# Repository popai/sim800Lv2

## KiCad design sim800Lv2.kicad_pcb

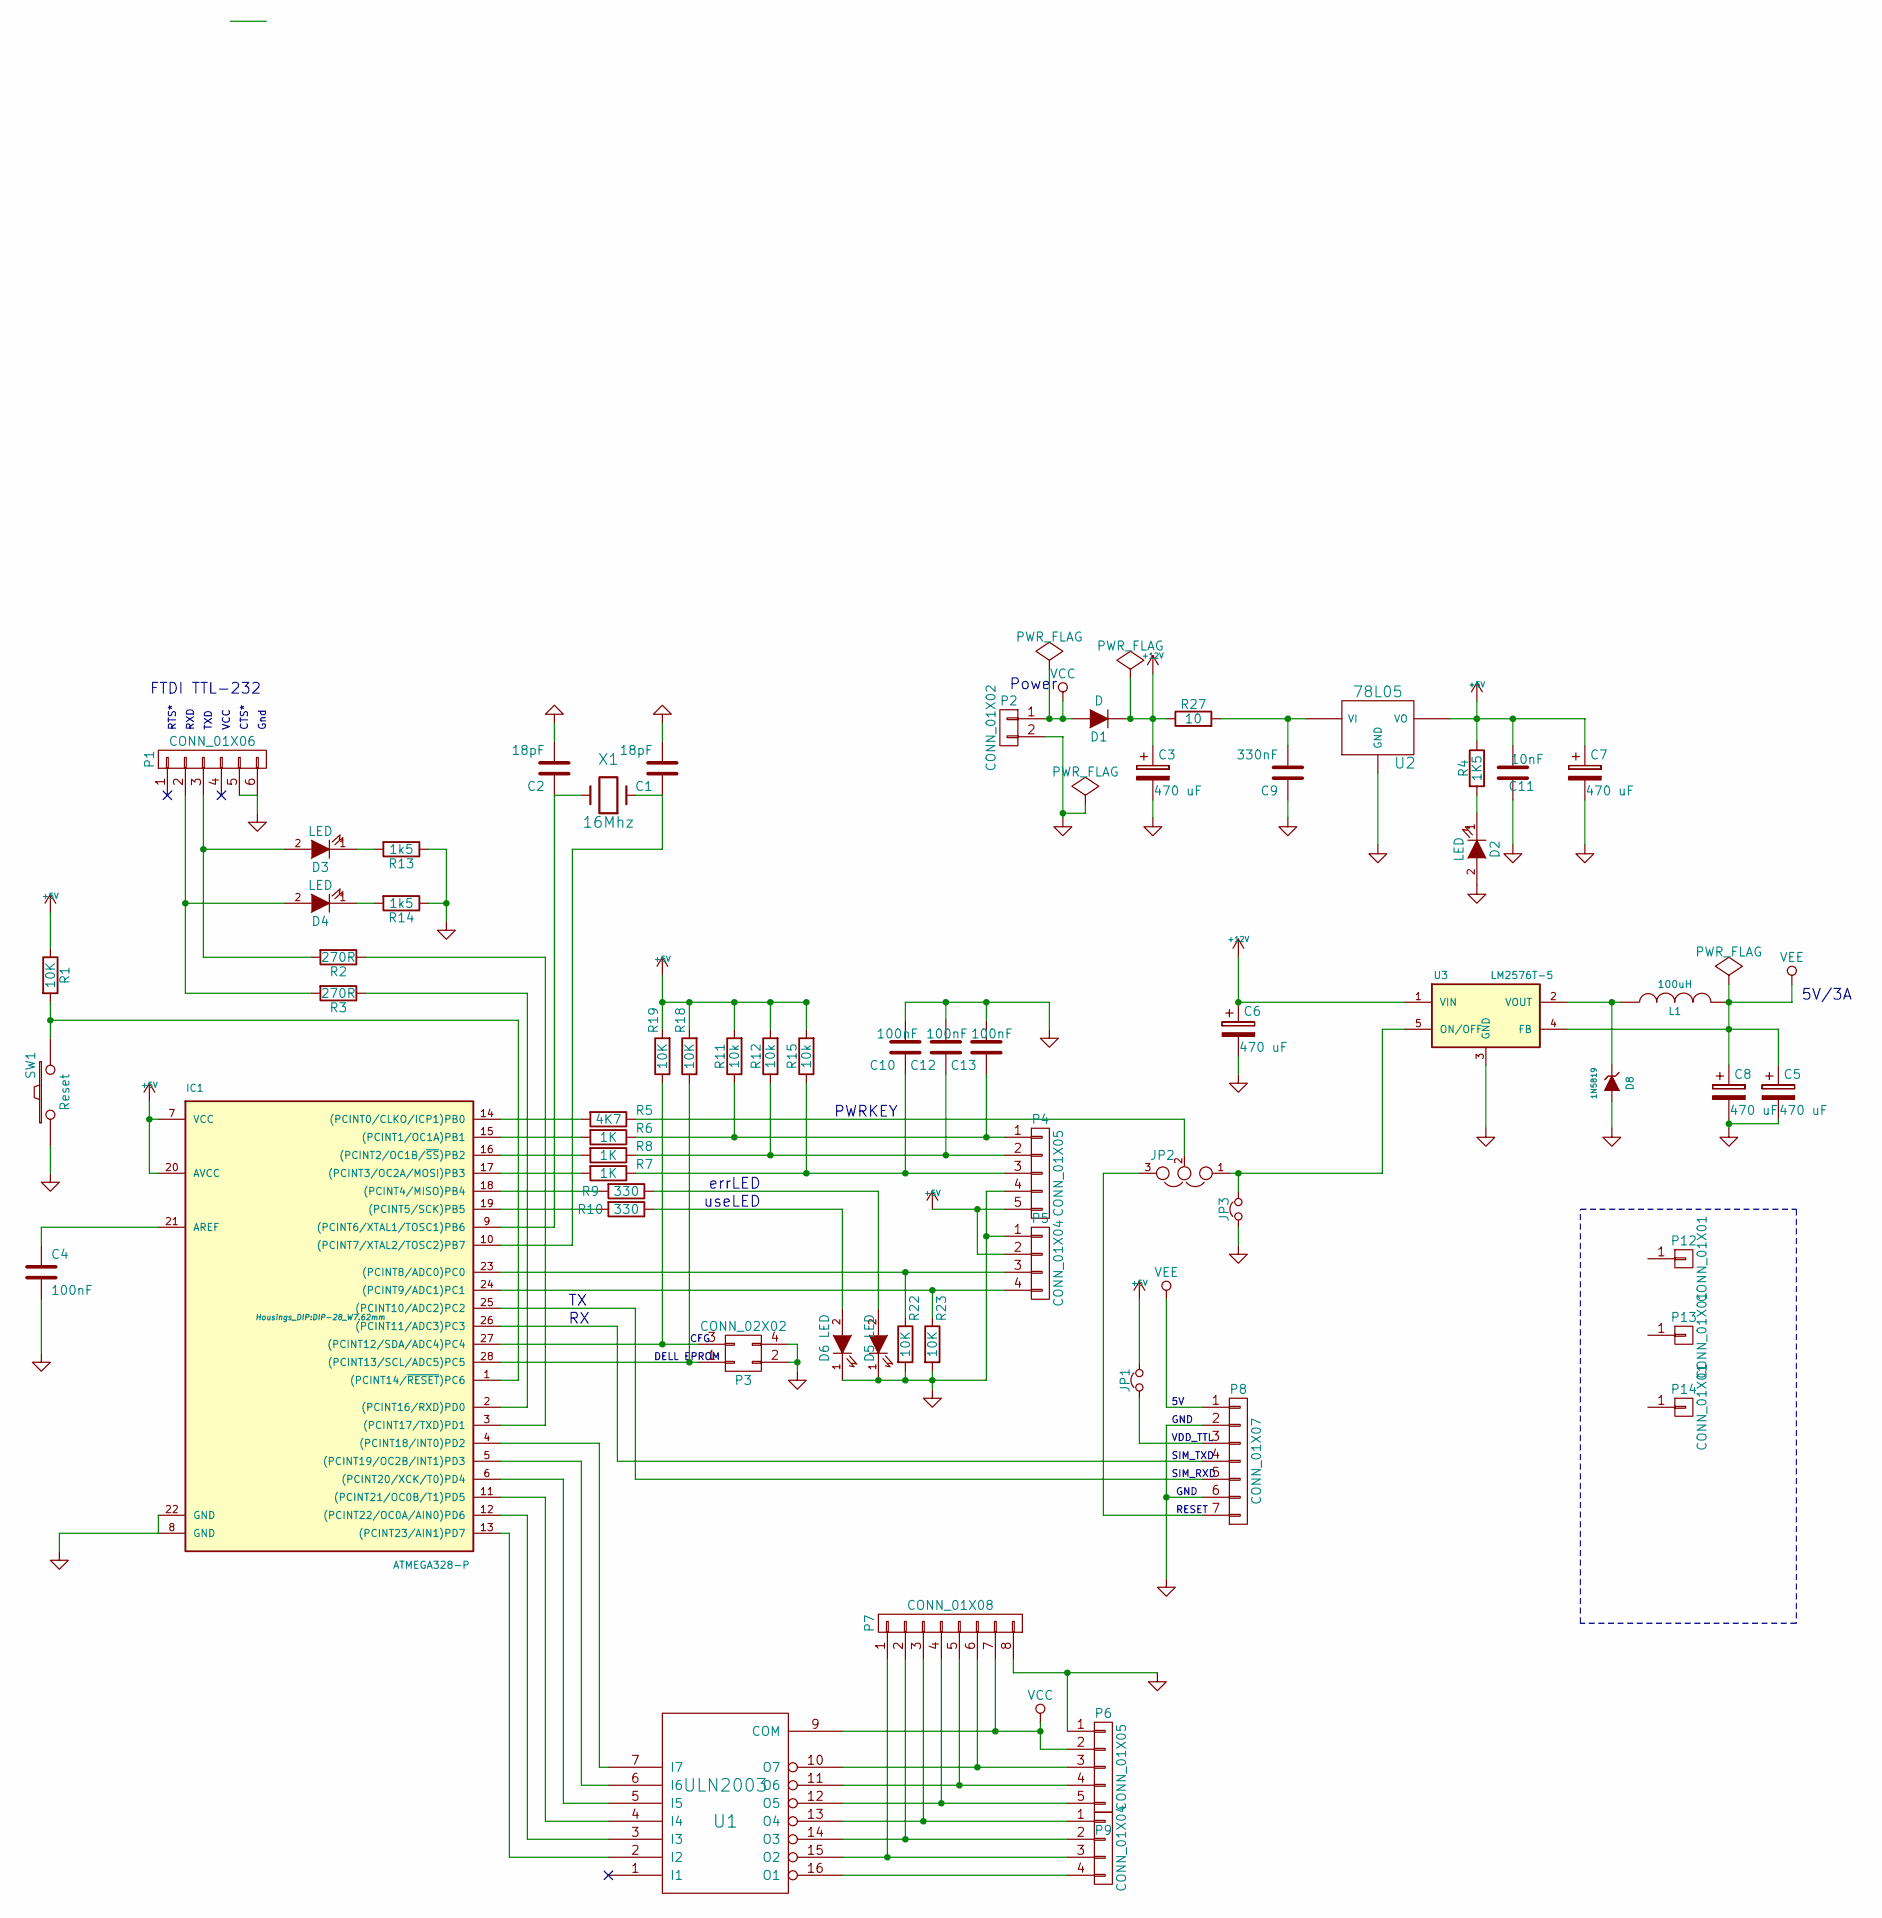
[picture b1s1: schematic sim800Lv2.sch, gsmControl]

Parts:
C1, C2: 18pF; C_Disc_D3_P2.5
C3, C5, C6, C7, C8: 470 uF; C_Radial_D8_L11.5_P3.5
C4, C10, C12, C13: 100nF; C_Rect_L7_W2_P5
C9: 330nF; C_Rect_L7_W2_P5
C11: 10nF; C_Rect_L7_W2_P5
D1: D; Diode_DO-35_SOD27_Horizontal_RM10
D2, D3, D4, D5, D6: LED; LED-3MM
D8: 1N5819; Diode_DO-35_SOD27_Horizontal_RM10
IC1: ATMEGA328-P; DIP-28_W7.62mm
JP1: Jumper_NC_Small; Resistor_Horizontal_RM7mm
JP2: JUMPER3; Pin_Header_Straight_1x03
JP3: Jumper_NC_Small; R_0603_HandSoldering
L1: 100uH; INDUCTOR_V
P1: CONN_01X06; Pin_Header_Straight_1x06
P2: CONN_01X02; Socket_MOLEX-KK-RM3-96mm_Lock_2pin_straight
P3: CONN_02X02; Pin_Header_Straight_2x02
P4, P6: CONN_01X05; Socket_MOLEX-KK-RM3-96mm_Lock_5pin_straight
P5, P9: CONN_01X04; Socket_MOLEX-KK-RM3-96mm_Lock_4pin_straight
P7: CONN_01X08; Pin_Header_Straight_1x08
P8: CONN_01X07; Socket_Strip_Straight_1x07
P12, P13, P14: CONN_01X01; TROU
R1, R18, R19, R22, R23: 10K; R4
R2, R3: 270R; R4
R4: 1K5; R4
R5: 4K7; R4
R6, R7, R8: 1K; R4
R9, R10: 330; R4
R11, R12, R15: 10k; R4
R13, R14: 1k5; R4
R27: 10; R4-5
SW1: Reset; SW_PUSH_SMALL
U1: ULN2003; DIP-16_W7.62mm
U2: 78L05; TO-220_Neutral123_Vertical_LargePads
U3: LM2576T-5; Pentawatt_Neutral_Staggered_Verical_TO220-5-T05D
X1: 16Mhz; Crystal_HC49-U_Vertical

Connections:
+5V: C7.1, C11.2, IC1.7 (VCC), IC1.20 (AVCC), JP1.2, P4.5, P5.2, R1.1, R4.1, R11.2, R12.2, R15.2, R18.2, R19.2, U2.VO
+12V: C3.1, C6.1, D1.1 (K), R27.1, U3.1 (VIN)
GND: C1.2, C2.2, C3.2, C4.2, C5.2, C6.2, C7.2, C8.2, C9.1, C10.2, C11.1, C12.2, C13.2, D2.2 (A), D5.1 (K), D6.1 (K), D8.2 (A), IC1.8 (GND), IC1.22 (GND), JP3.1, P1.5, P1.6, P2.2, P3.2, P3.4, P4.4, P5.1, P6.1, P7.8, P8.2, P8.6, R13.1, R14.1, R22.2, R23.2, SW1.1, U1.8 (GND), U2.GND, U3.3 (GND)
unnamed: C1.1, IC1.10 ((PCINT7/XTAL2/TOSC2)PB7), X1.1
unnamed: C2.1, IC1.9 ((PCINT6/XTAL1/TOSC1)PB6), X1.2
unnamed: C4.1, IC1.21 (AREF)
unnamed: C9.2, R27.2, U2.VI
unnamed: C10.1, P4.3, R7.1, R15.1
unnamed: C12.1, P4.2, R8.1, R12.1
unnamed: C13.1, P4.1, R6.1, R11.1
unnamed: D2.1 (K), R4.2
unnamed: D3.1 (K), R13.2
unnamed: D3.2 (A), P1.3, R2.2
unnamed: D4.1 (K), R14.2
unnamed: D4.2 (A), P1.2, R3.2
unnamed: D5.2 (A), R9.1
unnamed: D6.2 (A), R10.1
unnamed: D8.1 (K), L1.1, U3.2 (VOUT)
unnamed: IC1.1 ((PCINT14/~RESET~)PC6), R1.2, SW1.2
unnamed: IC1.2 ((PCINT16/RXD)PD0), R3.1
unnamed: IC1.3 ((PCINT17/TXD)PD1), R2.1
unnamed: IC1.4 ((PCINT18/INT0)PD2), U1.7 (I7)
unnamed: IC1.5 ((PCINT19/OC2B/INT1)PD3), U1.6 (I6)
unnamed: IC1.6 ((PCINT20/XCK/T0)PD4), U1.5 (I5)
unnamed: IC1.11 ((PCINT21/OC0B/T1)PD5), U1.4 (I4)
unnamed: IC1.12 ((PCINT22/OC0A/AIN0)PD6), U1.3 (I3)
unnamed: IC1.13 ((PCINT23/AIN1)PD7), U1.2 (I2)
unnamed: IC1.14 ((PCINT0/CLKO/ICP1)PB0), R5.2
unnamed: IC1.15 ((PCINT1/OC1A)PB1), R6.2
unnamed: IC1.16 ((PCINT2/OC1B/~SS~)PB2), R8.2
unnamed: IC1.17 ((PCINT3/OC2A/MOSI)PB3), R7.2
unnamed: IC1.18 ((PCINT4/MISO)PB4), R9.2
unnamed: IC1.19 ((PCINT5/SCK)PB5), R10.2
unnamed: IC1.23 ((PCINT8/ADC0)PC0), P5.3, R22.1
unnamed: IC1.24 ((PCINT9/ADC1)PC1), P5.4, R23.1
unnamed: IC1.25 ((PCINT10/ADC2)PC2), P8.5
unnamed: IC1.26 ((PCINT11/ADC3)PC3), P8.4
unnamed: IC1.27 ((PCINT12/SDA/ADC4)PC4), P3.3, R19.1
unnamed: IC1.28 ((PCINT13/SCL/ADC5)PC5), P3.1, R18.1
unnamed: JP1.1, P8.3
unnamed: JP2.1, JP3.2, U3.5 (ON/OFF)
unnamed: JP2.2, R5.1
unnamed: JP2.3, P8.7
unnamed: P6.3, P7.6, U1.10 (O7)
unnamed: P6.4, P7.5, U1.11 (O6)
unnamed: P6.5, P7.4, U1.12 (O5)
unnamed: P7.1, P9.3, U1.15 (O2)
unnamed: P7.2, P9.2, U1.14 (O3)
unnamed: P7.3, P9.1, U1.13 (O4)
unnamed: P9.4, U1.16 (O1)
VCC: D1.2 (A), P2.1, P6.2, P7.7, U1.9 (COM)
VEE: C5.1, C8.1, L1.2, P8.1, U3.4 (FB)

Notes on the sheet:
errLED
useLED
Power
Gnd
CTS*
VCC
TXD
RXD
RTS*
FTDI TTL-232
DELL EPROM
CFG
5V/3A
PWRKEY
GND
VDD_TTL
SIM_TXD
SIM_RXD
RESET

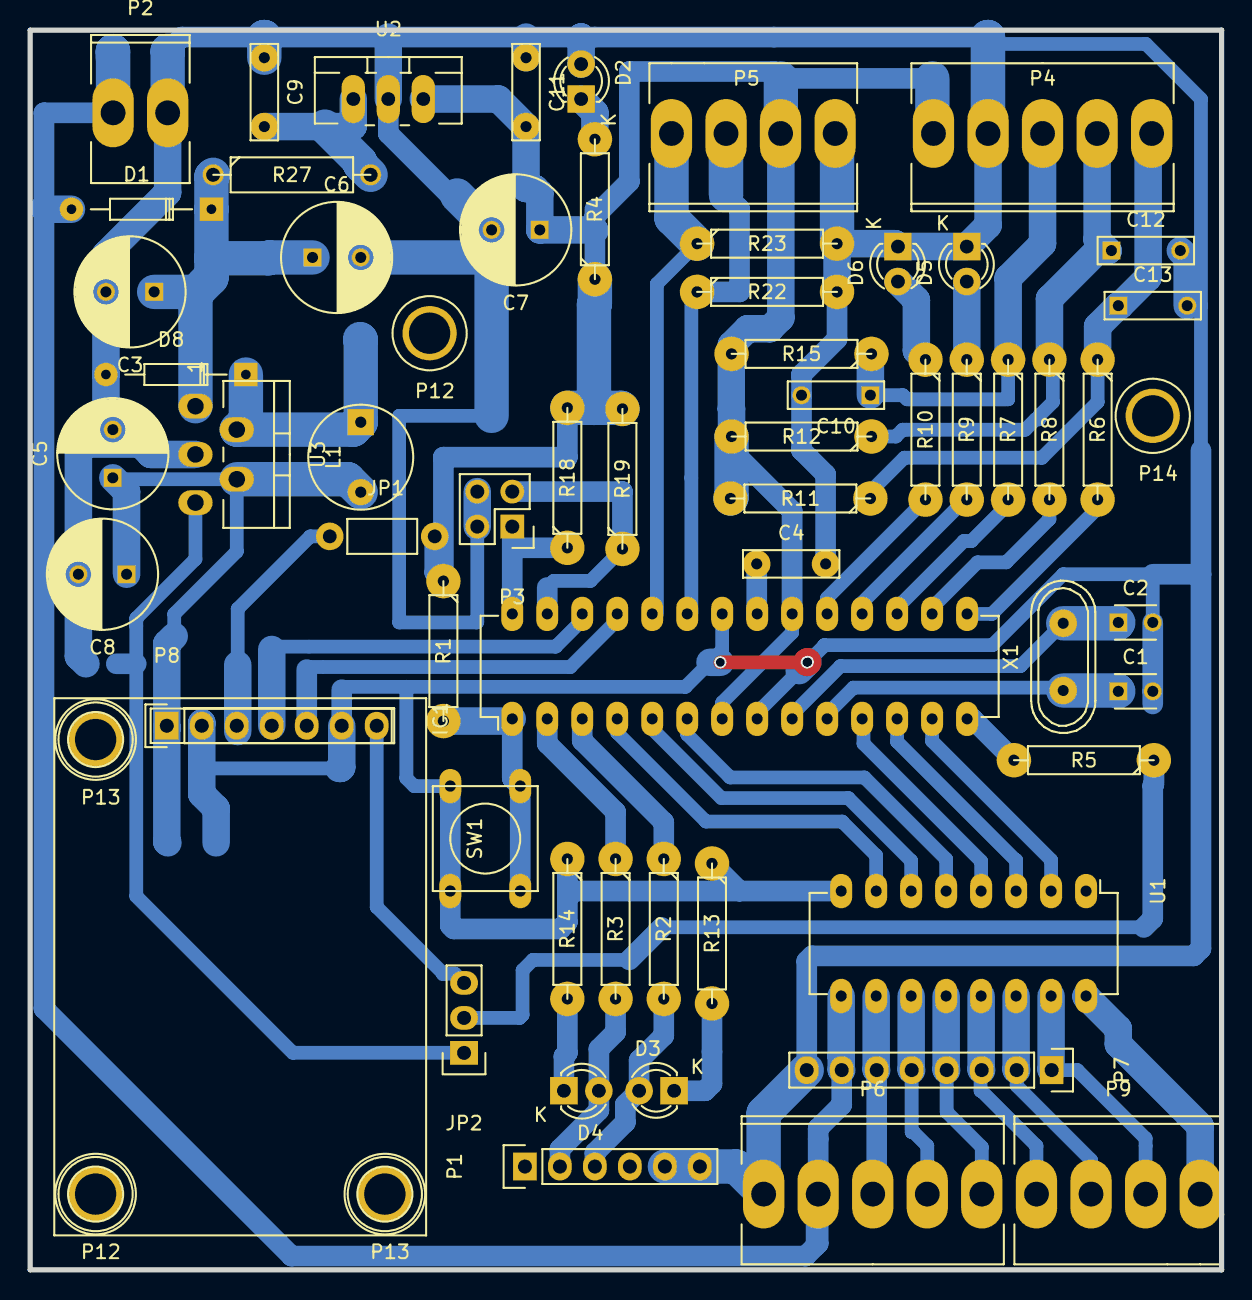
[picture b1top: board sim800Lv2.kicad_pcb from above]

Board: 2 copper layers, 86.5 x 90.0 mm, 64 parts (1 on the bottom side), 52 nets.

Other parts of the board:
P12#2, P13#2: CONN_01X01; TROU

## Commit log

2016-02-06 :space_invader: Added .gitattributes & .gitignore files
2016-02-06 conntroler hardware
    Atmega328 + modul Sim800L
